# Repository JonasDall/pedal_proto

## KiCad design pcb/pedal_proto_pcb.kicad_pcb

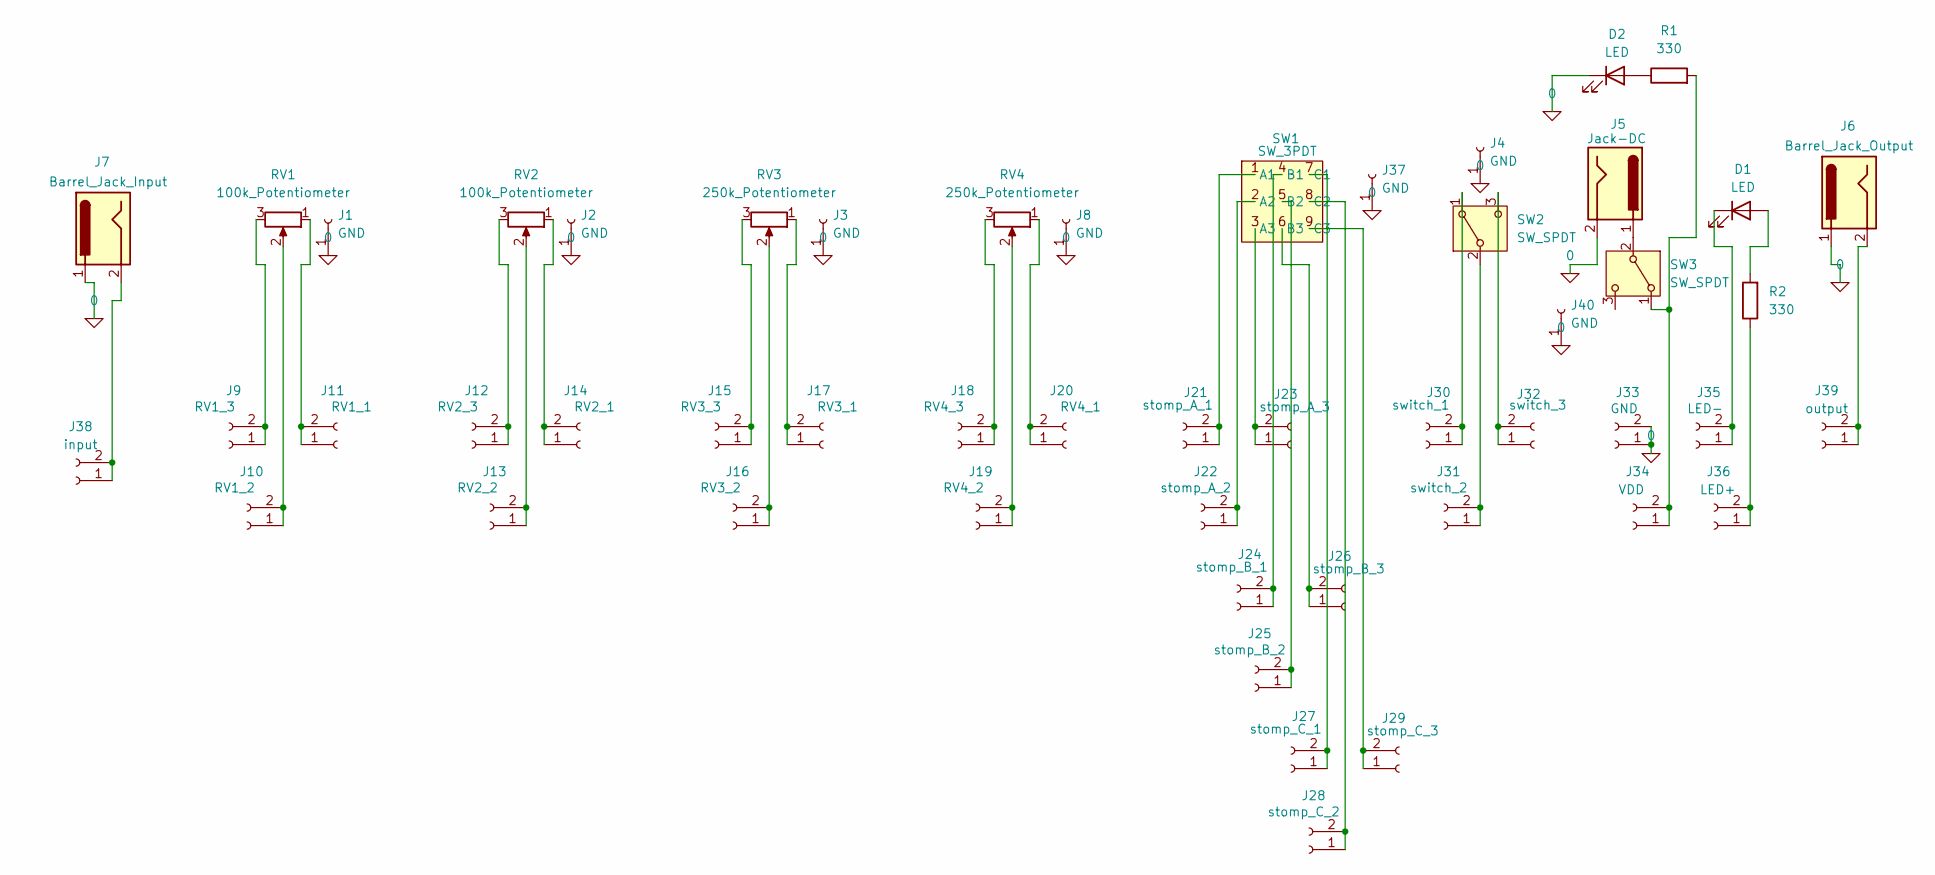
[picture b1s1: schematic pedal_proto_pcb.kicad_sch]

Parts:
D1, D2: LED; LED_D4.0mm
J1, J2, J3, J4, J8, J37, J40: GND; PinHeader_1x01_P2.54mm_Vertical
J5: Jack-DC; Barrel_Plug_5.5mmx2.1mm
J6: Barrel_Jack_Output; PinHeader_1x02_P2.54mm_Vertical
J7: Barrel_Jack_Input; PinHeader_1x02_P2.54mm_Vertical
J9: RV1_3; PinHeader_1x02_P2.54mm_Vertical
J10: RV1_2; PinHeader_1x02_P2.54mm_Vertical
J11: RV1_1; PinHeader_1x02_P2.54mm_Vertical
J12: RV2_3; PinHeader_1x02_P2.54mm_Vertical
J13: RV2_2; PinHeader_1x02_P2.54mm_Vertical
J14: RV2_1; PinHeader_1x02_P2.54mm_Vertical
J15: RV3_3; PinHeader_1x02_P2.54mm_Vertical
J16: RV3_2; PinHeader_1x02_P2.54mm_Vertical
J17: RV3_1; PinHeader_1x02_P2.54mm_Vertical
J18: RV4_3; PinHeader_1x02_P2.54mm_Vertical
J19: RV4_2; PinHeader_1x02_P2.54mm_Vertical
J20: RV4_1; PinHeader_1x02_P2.54mm_Vertical
J21: stomp_A_1; PinHeader_1x02_P2.54mm_Vertical
J22: stomp_A_2; PinHeader_1x02_P2.54mm_Vertical
J23: stomp_A_3; PinHeader_1x02_P2.54mm_Vertical
J24: stomp_B_1; PinHeader_1x02_P2.54mm_Vertical
J25: stomp_B_2; PinHeader_1x02_P2.54mm_Vertical
J26: stomp_B_3; PinHeader_1x02_P2.54mm_Vertical
J27: stomp_C_1; PinHeader_1x02_P2.54mm_Vertical
J28: stomp_C_2; PinHeader_1x02_P2.54mm_Vertical
J29: stomp_C_3; PinHeader_1x02_P2.54mm_Vertical
J30: switch_1; PinHeader_1x02_P2.54mm_Vertical
J31: switch_2; PinHeader_1x02_P2.54mm_Vertical
J32: switch_3; PinHeader_1x02_P2.54mm_Vertical
J33: GND; PinHeader_1x02_P2.54mm_Vertical
J34: VDD; PinHeader_1x02_P2.54mm_Vertical
J35: LED-; PinHeader_1x02_P2.54mm_Vertical
J36: LED+; PinHeader_1x02_P2.54mm_Vertical
J38: input; PinHeader_1x02_P2.54mm_Vertical
J39: output; PinHeader_1x02_P2.54mm_Vertical
R1, R2: 330; R_Axial_DIN0309_L9.0mm_D3.2mm_P12.70mm_Horizontal
RV1, RV2: 100k_Potentiometer; Lug_Pot
RV3, RV4: 250k_Potentiometer; Lug_Pot
SW1: SW_3PDT; 3PDT
SW2, SW3: SW_SPDT; SPDT

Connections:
0: D2.1 (K), J1.1, J2.1, J3.1, J4.1, J5.2, J6.1, J7.1, J8.1, J33.1, J33.2, J37.1, J40.1
unnamed: D1.2 (A), R2.2
unnamed: D1.1 (K), J35.1, J35.2
unnamed: D2.2 (A), R1.1
unnamed: J9.1, J9.2, RV1.3
unnamed: J10.1, J10.2, RV1.2
unnamed: J11.1, J11.2, RV1.1
unnamed: J12.1, J12.2, RV2.3
unnamed: J13.1, J13.2, RV2.2
unnamed: J14.1, J14.2, RV2.1
unnamed: J15.1, J15.2, RV3.3
unnamed: J16.1, J16.2, RV3.2
unnamed: J17.1, J17.2, RV3.1
unnamed: J18.1, J18.2, RV4.3
unnamed: J19.1, J19.2, RV4.2
unnamed: J20.1, J20.2, RV4.1
unnamed: J21.1, J21.2, SW1.1 (A1)
unnamed: J22.1, J22.2, SW1.2 (A2)
unnamed: J23.1, J23.2, SW1.3 (A3)
unnamed: J24.1, J24.2, SW1.4 (B1)
unnamed: J25.1, J25.2, SW1.5 (B2)
unnamed: J26.1, J26.2, SW1.6 (B3)
unnamed: J27.1, J27.2, SW1.7 (C1)
unnamed: J28.1, J28.2, SW1.8 (C2)
unnamed: J29.1, J29.2, SW1.9 (C3)
unnamed: J30.1, J30.2, SW2.1 (A)
unnamed: J31.1, J31.2, SW2.2 (B)
unnamed: J32.1, J32.2, SW2.3 (C)
unnamed: J34.1, J34.2, R1.2, SW3.1 (A)
unnamed: J36.1, J36.2, R2.1
unnamed: J7.2, J38.1, J38.2
unnamed: J6.2, J39.1, J39.2
unnamed: J5.1, SW3.2 (B)

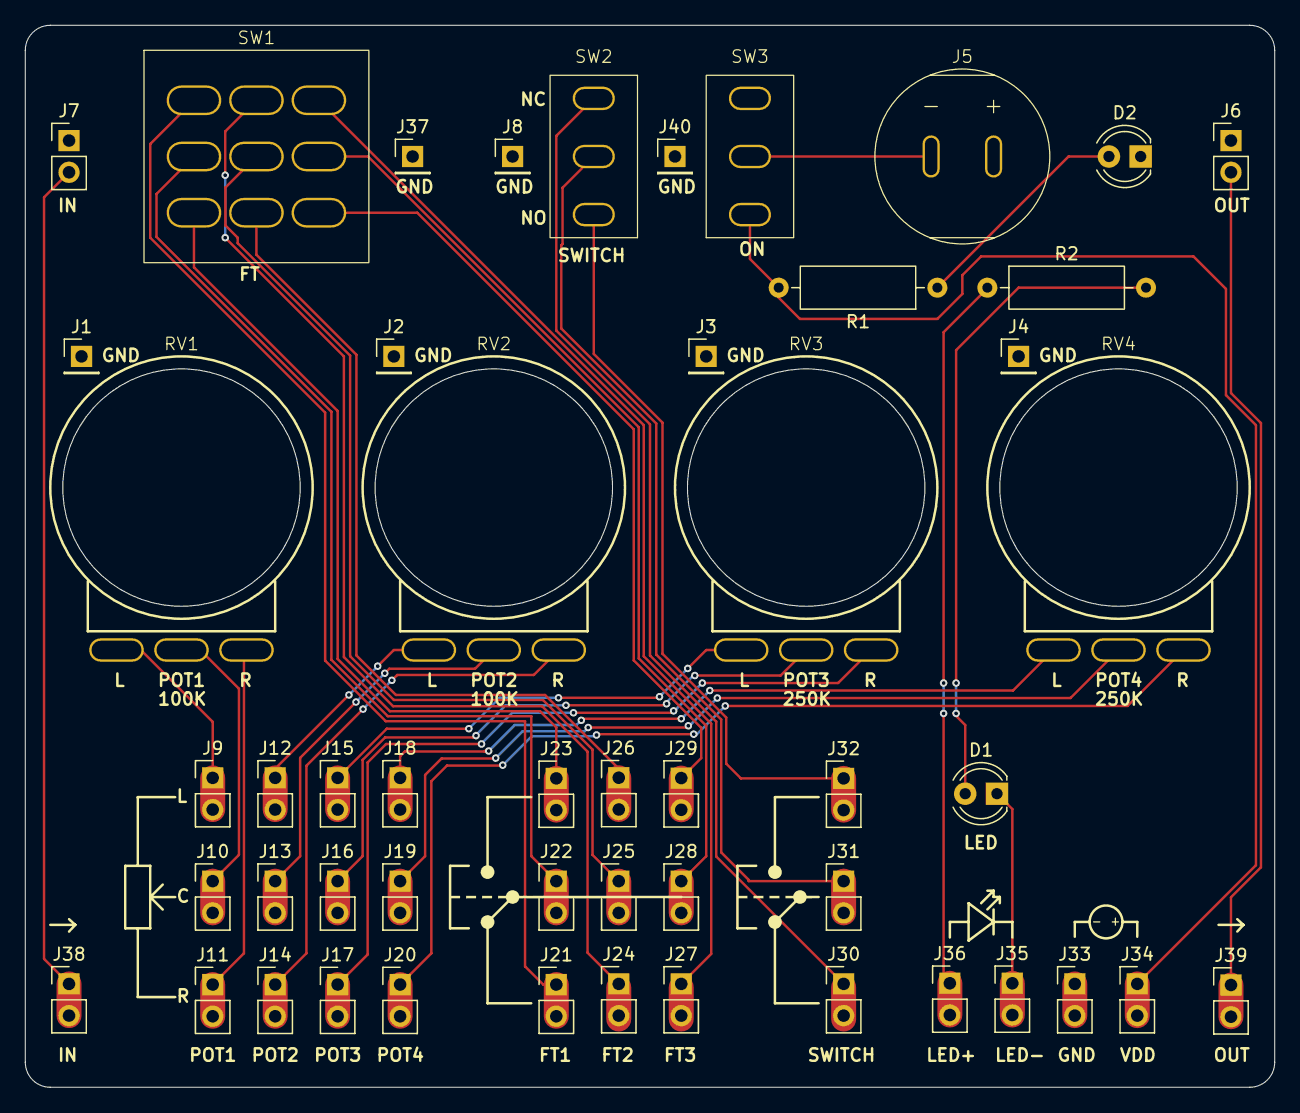
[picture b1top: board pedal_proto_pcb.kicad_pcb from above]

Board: 2 copper layers, 100.0 x 85.0 mm, 51 parts (0 on the bottom side), 33 nets.

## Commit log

2026-04-08 feat: init
2026-04-09 feat: board progress
2026-04-10 feat: started work on cover
2026-04-10 feat: completed lid
2026-04-10 feat: started schematic
2026-04-10 feat: pcb done
2026-04-11 feat: cad progress
2026-04-12 feat: new board model
2026-04-12 feat: updated pcb
2026-04-13 feat: added GND, pwr led and prw switch
2026-04-13 feat: began routing
2026-04-18 feat: almost done
2026-04-18 feat: layout done
2026-04-18 feat: layout changes
2026-04-18 feat: completed pcb
2026-04-18 feat: added pcb to print
2026-05-07 feat: board complete
2026-05-08 feat: added test print
